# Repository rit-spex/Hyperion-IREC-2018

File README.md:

# IREC-Hyperion

###### Overview
Every year Spaceport America host the Intercollegiate Rocket and Engineering Competition or IREC. Teams for colleges from across the country meet to compete in these events. The 2018 SA Cup will be held June 19-23, 2018, with events held in Las Cruces, NM. RIT SPEX will be partnering with RIT Launch Initiative to deliver our first entry into the competition. Launch Initiative will build the rocket, SPEX will provide the payload. Our goal is to design and build a scientific payload to compete in the intercollegiate rocket engineering competition.

###### Repository Contents

* ***/hardware*** - Hardware design documents
* ***/IREC-Hyperion Documentation*** - Documentation files regarding the Hyperion project
* ***/IREC-Hyperion Drop Test*** - Files regarding drop tests
* ***/IREC-Hyperion HABnet Data Feeder*** - Ground station software which collects data transmitted from payload
* ***/IREC-Hyperion Protocol*** - The Hyperion protocol software library
* ***/IREC-Hyperion System*** - System source files and libraries for the Hyperion payload
* ***/IREC-Hyperion Tests*** - Hyperion test resources 

###### Mission Patch

###### Hardware Modules
- Teensy 3.6
- Sparkfun LIS331
- Sparkfun LSM9DS1
- Adafruit BME280
- Sparkfun CCS811
- RFM_9X LoRa
- PerfectFlite StratoLogger CF

###### Contributors

Daniel Mitchell

Alec Herbert

Thomas James Hall

Dylan R. Wagner

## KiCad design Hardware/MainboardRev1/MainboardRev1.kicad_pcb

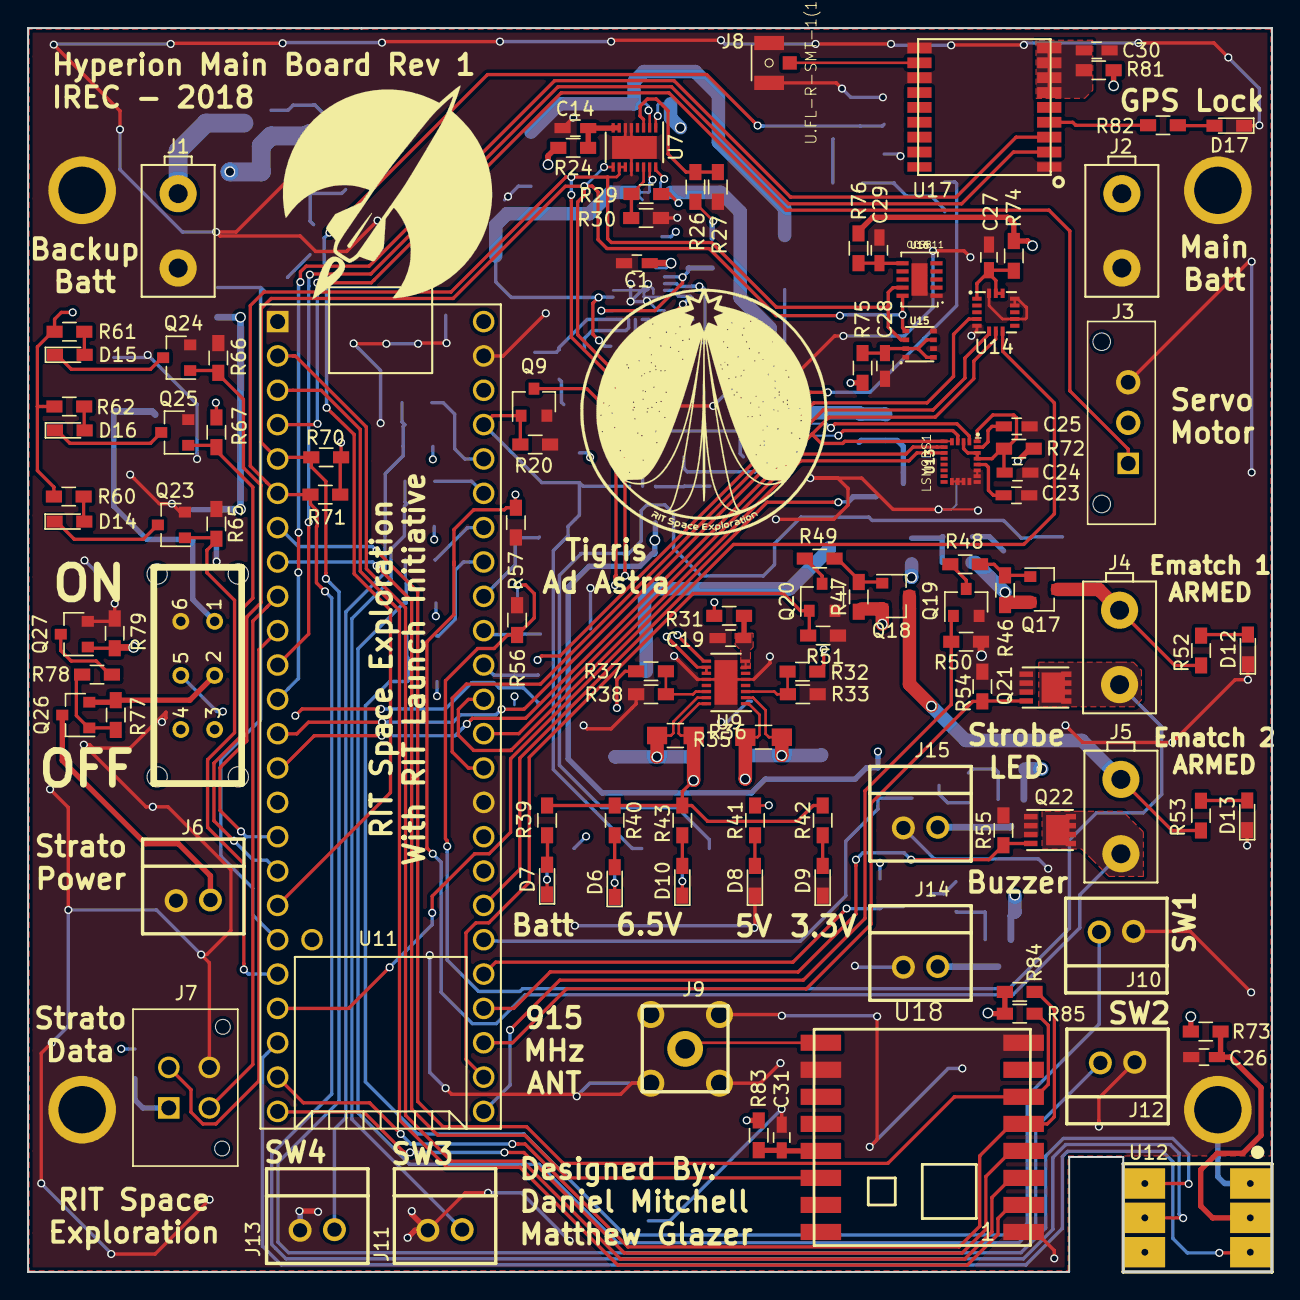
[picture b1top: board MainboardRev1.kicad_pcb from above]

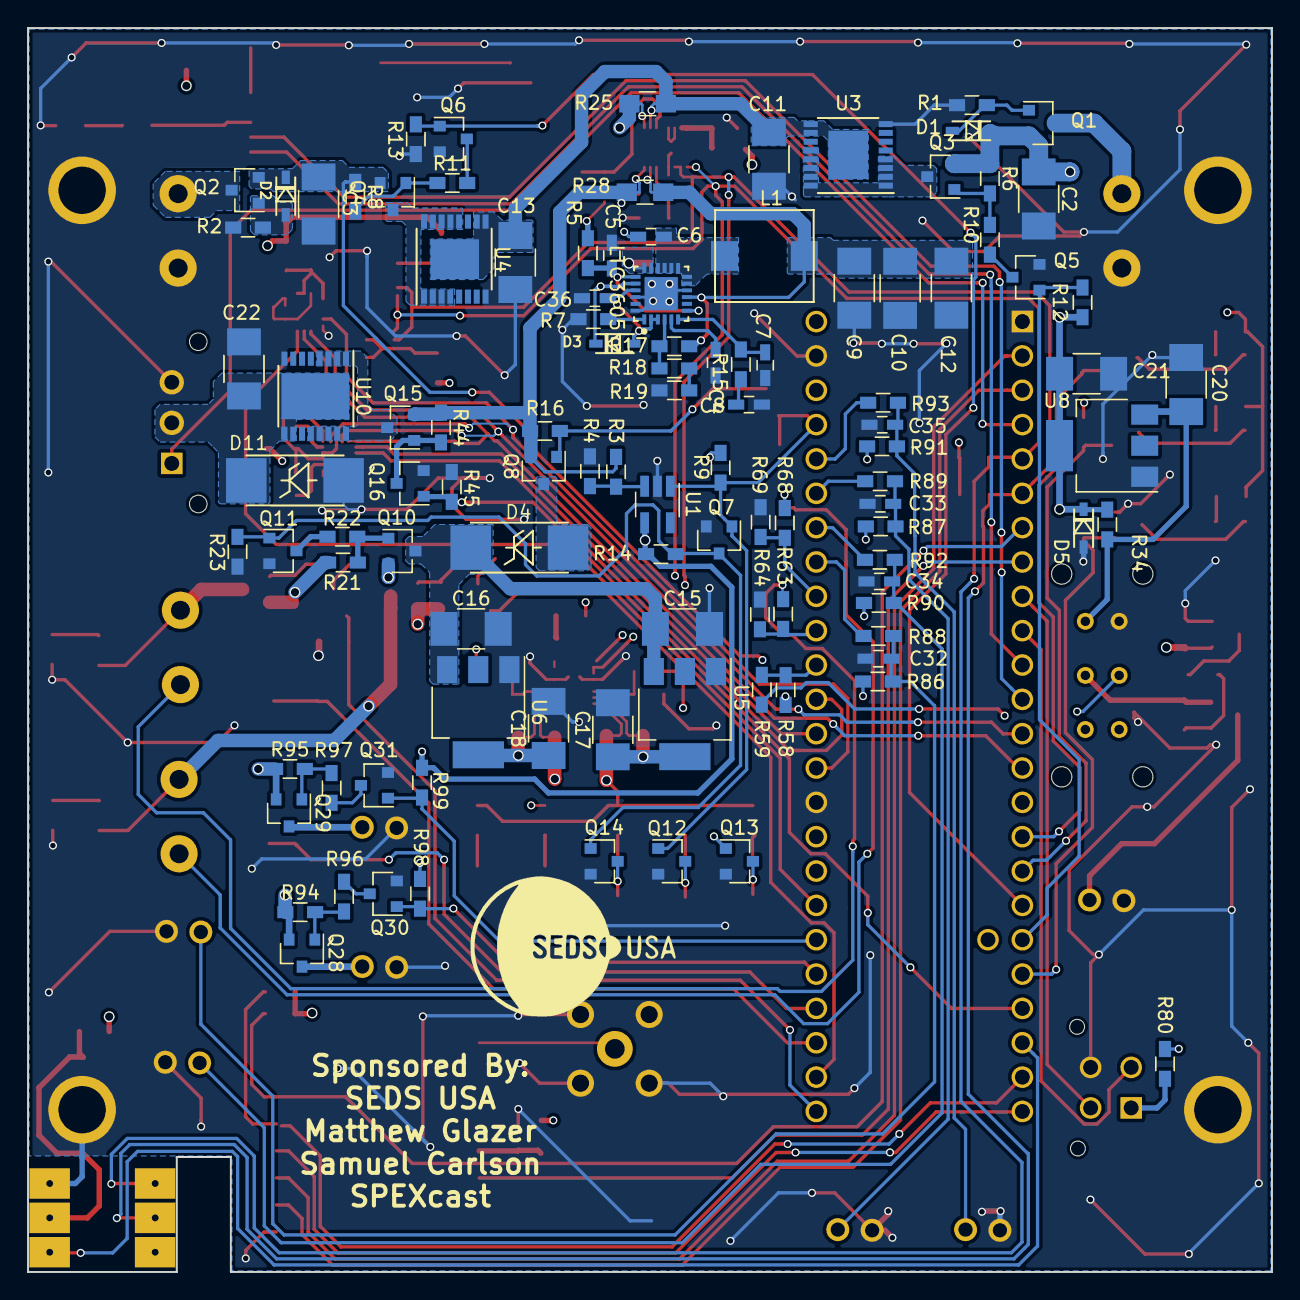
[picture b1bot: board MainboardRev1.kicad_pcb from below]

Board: 4 copper layers, 92.0 x 92.0 mm, 222 parts (106 on the bottom side), 141 nets.

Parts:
C1, C5, C6, C14, C19, C24, C26, C27, C28, C29, C30, C31: 0.1uF; C_0603_HandSoldering
C2, C3, C9, C10, C11, C12, C13, C15, C16, C17, C18, C20, C21, C22: 47uF; C_1210_HandSoldering
C4: .01uF; C_0603_HandSoldering
C7: 10pF; C_0603_HandSoldering
C8: 220pF; C_0603_HandSoldering
C23: 10000pF; C_0603_HandSoldering
C25: 100nF; C_0603_HandSoldering
C32, C33, C34, C35: 10nF; C_0603_HandSoldering
C36: C_0603_HandSoldering
D1, D2: 5.6V; SOD-323_Diode
D3: CMDSH2-3; SOD-323_Diode
D4, D11: SL42-E3/57T; DO-214AB_Zener
D5: +3.3V_Zener; SOD-323_Diode
D6, D7, D8, D9, D14: Green; LED_0603_HandSoldering
D10, D16: Red; LED_0603_HandSoldering
D12, D13: RED; LED_0603_HandSoldering
D15: Blue; LED_0603_HandSoldering
D17: BLUE; LED_0603_HandSoldering
J1: BACKUP_BATT: 1586038-2; CONN_2POS_VERT_TE_CONN
J2: MAIN_BATT: 1586038-2; CONN_2POS_VERT_TE_CONN
J3: Servo_Control; Molex_Microfit3_Header_01x03_Straight
J4: EMATCH_1: 1586038-2; CONN_2POS_VERT_TE_CONN
J5: EMATCH_2: 1586038-2; CONN_2POS_VERT_TE_CONN
J6: Stratologger_PWR: 1586038-2; CONN_2POS_VERT_TE_CONN_LOCK_5-103669-1
J7: Stratologger_DATA; 4-Pin_Molex_Vertical
J8: U.FL-R-SMT-1(10); HRS_U.FL-R-SMT-1(10)
J9: 0733910320 [915MHz SMA]; CONN_RP-SMA_Right_Angle_0733910320
J10: Switch_1; CONN_2POS_VERT_TE_CONN_LOCK_5-103669-1
J11: Switch_3; CONN_2POS_VERT_TE_CONN_LOCK_5-103669-1
J12: Switch_2; CONN_2POS_VERT_TE_CONN_LOCK_5-103669-1
J13: Switch_4; CONN_2POS_VERT_TE_CONN_LOCK_5-103669-1
J14: Buzzer; CONN_2POS_VERT_TE_CONN_LOCK_5-103669-1
J15: Strobe; CONN_2POS_VERT_TE_CONN_LOCK_5-103669-1
L1: RLF7030T-2R2M5R4 [2.2uH]; IND_RLF7030
MH1, MH2, MH3, MH4: Mounting Hole; Mounting_Hole_3.50mm
Q1, Q2, Q3, Q4, Q8, Q10, Q15, Q17, Q18, Q26, Q28, Q29: SSM3J328R; SOT-23
Q5, Q6, Q7, Q9, Q11, Q12, Q13, Q14, Q16, Q19, Q20, Q23, Q24, Q25, Q27, Q30, Q31: NTR4003; SOT-23
Q21, Q22: SIS612EDNT-T1-GE3; PowerPAK_1212-8S
R1, R2, R34: 100k; R_0603_HandSoldering
R3: 140k; R_0603_HandSoldering
R4, R12, R13, R18, R20, R23, R45, R50, R51, R54, R55, R65, R66, R67, R70, R71, R77, R79, R84, R85, R86, R87, R90, R91, R98, R99: 10k; R_0603_HandSoldering
R5, R24, R31, R72, R73, R74, R75, R76, R81, R83: 10; R_0603_HandSoldering
R6, R8, R16, R21, R44, R46, R47, R94, R95: 10K; R_0603_HandSoldering
R7: 200k; R_0603_HandSoldering
R9, R14, R52, R53: 510; R_0603_HandSoldering
R10, R11, R22, R48, R49, R78, R96, R97: 12k; R_0603_HandSoldering
R15: 16k; R_0603_HandSoldering
R17: 118k; R_0603_HandSoldering
R19: 2k; R_0603_HandSoldering
R25, R28: 10m; R_0805_HandSoldering
R26, R29, R32, R37, R56, R57: 1M; R_0603_HandSoldering
R27, R30, R33, R38: 11.5k; R_0603_HandSoldering
R35, R36: 25m; R_0805_HandSoldering
R39, R40, R42, R60, R61, R82: 80; R_0603_HandSoldering
R41: 470; R_0603_HandSoldering
R43, R62: 150; R_0603_HandSoldering
R58, R63, R68: 45.3k; R_0603_HandSoldering
R59, R64, R69: 11.3k; R_0603_HandSoldering
R80: 0; R_0603_HandSoldering
R88, R89, R92, R93: 1k; R_0603_HandSoldering
SW1: EG2201A [DPDT]; SW_DPDT_30V_200mA_EG2201A
U1: LT6703-3; SOT-23-5_HandSoldering
U2: LTC3605; QFN25_4x4mm_0.5mm_pitch
U3, U4: LTC4358; TSSOP-16-1EP_4.4x5mm_Pitch0.65mm
U5: LDL1117S50R; SOT-223_Tab_Pin_2
U6, U8: LDL1117S33R; SOT-223_Tab_Pin_2
U7, U9: LTC2992; DFN-16-1EP_3x4mm_Pitch0.45mm
U10: LTC4358; HTSSOP-16-1EP_4.4x5mm_Pitch0.65mm
U11: Teensy3.6; Teensy33_SidePinsAndVBatt
U12: ABPMANN030PG2A3; PRESSURE_TRANSDUCER_ABPMANN030PG2A3
U13: LSM9DS1; PQFN24P43_350X300X102L35X23N
U14: LIS331HH; LGA16_3x3mm_0.5mm_pitch
U15: BME280
U16: CCS811; SON60P270X400X110-11N
U17: ublox_max-m8q; MAX-M8
U18: RFM69HCW; RFM69HCW-XXXS2

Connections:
+3.3V: Q13.1, R24.2, R31.2, R35.1, R37.1, R67.1, R70.1, R71.1, R72.2, R73.2, R74.2, R75.2, R76.2, R80.2, R81.2, R83.2, R84.1, R85.1, R86.1, R87.1, R90.1, R91.1, U9.1
+3.3V_DIVIDER: R37.2, R38.1, U9.14
+3.3V_MSMT: C18.1, R35.2, U6.2, U9.2
+3.3V_STARTUP: C21.1, D5.1, Q27.1, R9.1, R12.1, R14.1, R34.1, R79.1, R98.1, R99.1, U1.4, U8.2
+5V: R32.1, R36.1, R39.2, R40.1, R42.2, R43.1, R60.2, R61.2, R62.2, U9.16, U11.53
+5V_DIVIDER: R32.2, R33.1, U9.3
+5V_MSMT: C17.1, R36.2, U5.2, U9.15
+6.5V: Q8.2, Q15.2, R3.1, R16.1, R28.1, R29.1, R44.1, U7.16
+6.5V_DIVIDER: R29.2, R30.1, U7.14
+6.5V_MSMT: C9.1, C10.1, C12.1, L1.2, R17.1, R28.2, U2.9, U7.15
BACKUP_BATT: C2.1, D1.1, Q1.2, Q3.2, Q26.2, R6.1, R77.1, SW1.2
BACKUP_BATT_EN: Q5.1, R12.2, U11.19
BATTERY_DIVIDER: R26.2, R27.1, U7.3
BATTERY_PWR: C1.1, Q10.2, Q17.2, Q18.2, Q28.2, Q29.2, R5.2, R21.1, R25.1, R26.1, R41.2, R46.1, R47.1, R94.1, R95.1, U2.17, U2.18, U7.1
BATTERY_PWR_MSMT: C11.1, C13.1, R25.2, U3.9, U3.10, U3.17, U4.9, U4.10, U4.17, U7.2
Buzzer_Disable: Q30.1, R98.2, U11.34
COMMS_CS_LORA: R84.2, U11.23, U18.5
COMMS_MISO: U11.3, U18.2
COMMS_MOSI: U11.2, U18.3
COMMS_RX: U11.11, U17.2
COMMS_SCLK: U11.24, U18.4
COMMS_TX: U11.12, U17.3
CONTROL_1: Q7.1, Q9.1, Q12.1, R9.2, R20.1, U1.1, U11.50
CONTROL_2: Q7.3, Q11.1, Q14.1, R14.2, R23.1
EMATCH_1_ANLG: R63.2, R64.1, U11.44
EMATCH_1_ARM: Q19.1, R50.1, U11.30
EMATCH_1_CHECK: J4.2, Q21.3, R56.1, R63.1
EMATCH_1_FIRE: Q21.1, R54.1, U11.32
EMATCH_2_ANLG: R68.2, R69.1, U11.45
EMATCH_2_ARM: Q20.1, R51.1, U11.31
EMATCH_2_CHECK: J5.2, Q22.3, R57.1, R68.1
EMATCH_2_FIRE: Q22.1, R55.1, U11.33
GND: C1.2, C2.2, C3.2, C4.2, C5.1, C7.2, C8.2, C9.2, C10.2, C11.2, C12.2, C13.2, C14.2, C15.2, C16.2, C17.2, C18.2, C19.2, C20.2, C21.2, C22.2, C23.2, C24.2, C25.2, C26.2, C27.2, C28.2, C29.2, C30.2, C31.2, C32.2, C33.2, C34.2, C35.2, C36.1, D5.2, D8.1, D9.1, D11.2, D12.1, D13.1, D17.1, J1.2, J2.2, J3.3, J6.2, J7.4, J8.2, J9.2, J10.2, J11.2, J12.2, J13.2, J14.2, J15.2, MH1.1, MH2.1, MH3.1, MH4.1, Q5.2, Q6.2, Q7.2, Q9.2, Q11.2, Q12.2, Q13.2, Q14.2, Q16.2, Q19.2, Q20.2, Q21.2, Q22.2, Q23.2, Q24.2, Q25.2, Q27.2, Q30.2, Q31.2, R1.2, R2.2, R4.2, R7.2, R13.2, R19.2, R20.2, R23.2, R27.2, R30.2, R33.2, R38.2, R45.2, R50.2, R51.2, R54.2, R55.2, R56.2, R57.2, R64.2, R65.1, R66.1, R69.2, R79.2, SW1.6, U1.2, U2.10, U2.22, U2.24, U2.25, U3.8, U4.8, U5.1, U6.1, U7.5, U7.6, U7.12, U7.17, U8.1, U9.5, U9.12, U9.17, U10.8, U11.1, U11.39, U11.52, U12.1, U13.14, U13.15, U13.16, U13.17, U13.18, U13.19, U13.20, U14.5, U14.10, U14.12, U14.13, U14.16, U15.1, U15.5, U15.7, U16.1, U16.11, U17.1, U17.10, U17.12, U18.1, U18.8, U18.10
INT_PRESSURE: U11.22, U12.3
LDO_FEED: C15.1, C16.1, D4.1, Q10.3, U5.3, U6.3
LED_BLUE: Q24.1, R66.2, U11.16
LED_GREEN: Q23.1, R65.2, U11.20
LED_RED: Q25.1, R67.2, U11.17
LORA_INT: U11.8, U18.14
LORA_RESET: R85.2, U11.7, U18.6
LSM_C1: C25.1, U13.24
LSM_CAP: C23.1, U13.21
MAIN_BATT: C3.1, D2.1, Q2.2, Q4.2, R8.1, R58.1
MAIN_BATT_ANLG: R58.2, R59.1, U11.43
MAIN_BATT_EN: Q6.1, R13.1, U11.18
MAIN_BATT_READ_EN: R59.2, SW1.5
unnamed: C4.1, U2.5
unnamed: C6.1, D3.1, U2.20
unnamed: C6.2, L1.1, U2.11, U2.12, U2.13, U2.14, U2.15, U2.16
unnamed: C7.1, R15.2, U2.6
unnamed: C8.1, R15.1
unnamed: C14.1, R24.1, U7.7, U7.8
unnamed: C19.1, R31.1, U9.7, U9.8
unnamed: C22.1, D11.1, J3.2, U10.9, U10.10, U10.17
unnamed: C24.1, R72.1, U13.1, U13.3, U13.22, U13.23
unnamed: C26.1, R73.1, U12.2
unnamed: C27.1, R74.1, U14.1, U14.14, U14.15
unnamed: C28.1, R75.1, U15.2, U15.6, U15.8
unnamed: C29.1, R76.1, U16.6
unnamed: C30.1, R81.1, U17.6, U17.7, U17.8, U17.9
unnamed: C31.1, R83.1, U18.13
unnamed: C32.1, J10.1, R86.2, R88.2
unnamed: C33.1, J11.1, R87.2, R89.2
unnamed: C34.1, J12.1, R90.2, R92.2
unnamed: C35.1, J13.1, R91.2, R93.2
unnamed: D1.2, Q1.1, R1.1
unnamed: D2.2, Q2.1, R2.1
unnamed: C36.2, D3.2, U2.2, U2.3, U2.21
unnamed: D4.2, Q8.3
unnamed: D6.1, Q12.3
unnamed: D6.2, R40.2
unnamed: D7.1, Q13.3
unnamed: D7.2, R39.1
unnamed: D8.2, R41.1
unnamed: D9.2, R42.1
unnamed: D10.1, Q14.3
unnamed: D10.2, R43.2
unnamed: D12.2, R52.1
unnamed: D13.2, R53.1
unnamed: D14.1, Q23.3
unnamed: D14.2, R60.1
unnamed: D15.1, Q24.3
unnamed: D15.2, R61.1
unnamed: D16.1, Q25.3
unnamed: D16.2, R62.1
unnamed: D17.2, R82.1
unnamed: J1.1, Q1.3
unnamed: J2.1, Q2.3
unnamed: J4.1, Q17.3, R52.2
unnamed: J5.1, Q18.3, R53.2
unnamed: J6.1, Q26.3
unnamed: J7.1, R80.1
unnamed: J8.1, U17.11
unnamed: J9.1, U18.9
unnamed: J14.1, Q28.3
unnamed: J15.1, Q29.3
unnamed: Q3.1, R6.2, R10.1
unnamed: Q3.3, U3.1, U3.2, U3.3, U3.4, U3.12, U3.13, U3.14, U3.15, U3.16
unnamed: Q4.1, R8.2, R11.1
unnamed: Q4.3, U4.1, U4.2, U4.3, U4.4, U4.12, U4.13, U4.14, U4.15, U4.16
unnamed: Q5.3, R10.2
unnamed: Q6.3, R11.2
unnamed: Q8.1, Q9.3, R16.2
unnamed: Q10.1, R21.2, R22.1
unnamed: Q11.3, R22.2
unnamed: Q15.1, Q16.3, R44.2
unnamed: Q15.3, U10.1, U10.2, U10.3, U10.4, U10.12, U10.13, U10.14, U10.15, U10.16
unnamed: Q17.1, R46.2, R48.1
unnamed: Q18.1, R47.2, R49.1
unnamed: Q19.3, R48.2
unnamed: Q20.3, R49.2
unnamed: Q26.1, R77.2, R78.1
unnamed: Q27.3, R78.2
unnamed: Q28.1, R94.2, R96.1
unnamed: Q29.1, R95.2, R97.1
unnamed: Q30.3, R96.2
unnamed: Q31.3, R97.2
unnamed: R3.2, R4.1, U1.3
unnamed: R7.1, U2.1
unnamed: R17.2, R18.1, U2.4
unnamed: R18.2, R19.1
unnamed: R82.2, U17.4
SENSORS_CS_AG: U11.41, U13.7
SENSORS_CS_LIS: U11.36, U14.8
SENSORS_CS_M: U11.42, U13.8
SENSORS_MISO: U11.14, U13.5, U13.6, U14.7
SENSORS_MOSI: U11.13, U13.4, U14.6
SENSORS_RX: J7.3, U11.9
SENSORS_SCL: R70.2, U7.9, U9.9, U11.5, U12.6, U15.4, U16.10
SENSORS_SCLK: U11.40, U13.2, U14.4
SENSORS_SDA: R71.2, U7.10, U7.11, U9.10, U9.11, U11.6, U12.5, U15.3, U16.9
SENSORS_TX: J7.2, U11.10
SERVO_PWM: J3.1, U11.4
SERVO_PWR_EN: Q16.1, R45.1, U11.21
STARTUP_BATT: C20.1, R34.2, SW1.1, U8.3
SVIN: C5.2, R5.1, U2.7, U2.19
SWITCH_1: R88.1, U11.46
SWITCH_2: R92.1, U11.47
SWITCH_3: R89.1, U11.48
SWITCH_4: R93.1, U11.49
Strobe_Disable: Q31.1, R99.2, U11.35

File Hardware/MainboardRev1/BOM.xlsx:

RIT Space Exploration - Hyperion Scientific Payload for the Intercollegiate Roc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
Ref | Description | Manf Part Number | Manf | Footprint | Purchase Link | Quantity | Price | Sub Total
C4 C23 C32 C33 C34 C35 | .01uF, 100V |  |  | 0603 | Digikey
C1 C5 C6 C14 C19 C24 C25 C26 C27 C28 C29 C30 C31 | 0.1uF, 50V |  |  | 0603 | Digikey
C7 | 10pF, 25V |  |  | 0603 | Digikey
C8 | 220pF, 100V |  |  | 0603 | Digikey
C2 C3 C9 C10 C11 C12 C13 C15 C16 C17 C18 C20 C21 C22 | 47uF, 16V |  |  | 1210 | Digikey
D5 | 3.3V Zener |  |  |  | Digikey
D1 D2 | 5.6V Zener |  |  |  | Digikey
D3 | Schottky Diode (Switching Regulator) |  |  |  | Digikey
D15 D17 | Blue LED | 3.3Vf, 20mA, 104mcd |  |  | Digikey
D6 D7 D8 D9 D14 | Green LED | 3.4Vf, 10mA, 98mcd |  |  | Digikey
D10 D12 D13 D16 | Red LED | 2Vf, 20mA, 104mcd |  |  | Digikey
D4 D11 | Schottky Diode 20V 4A |  |  |  | Digikey
J9 |  | CONN_RP-SMA_Right_Angle_0733910320 |  |  | Digikey
J1 J2 J4 J5 |  | CONN_2POS_VERT_TE_CONN |  |  | Digikey
Mates for Above |  |  |  |  | Digikey
J6 J10 J11 J12 J13 J14 J15 |  |  |  |  | Digikey
Mates for Above |  |  |  |  | Digikey
J3 |  | Molex_Microfit3_Header_01x03_Straight |  |  | Digikey
Mates for Above |  |  |  |  | Digikey
J7 |  | 4-Pin_Molex_Vertical |  |  | Digikey
Mates for Above |  |  |  |  | Digikey
J8 |  | HRS_U.FL-R-SMT-1(10) |  |  | Digikey
TE Connectivity AMP Pins |  |  |  |  | Digikey
Other TE Connectivity Pins??? |  |  |  |  | Digikey
Molex Pins |  |  |  |  | Digikey
 |  |  |  |  |  | 0 |  | 0
L1 | 2.2uH | RLF7030T-2R2M5R4 |  |  | Digikey
 |  |  |  |  |  | 0 |  | 0
Q5 Q6 Q7 Q9 Q11 Q12 Q13 Q14 Q16 Q19 Q20 Q23 Q24 Q25 Q27 Q30 Q31 |  | NTR4003 |  |  | Digikey
Q21 Q22 |  | SIS612EDNT-T1-GE3 |  |  | Digikey
Q1 Q2 Q3 Q4 Q8 Q10 Q15 Q17 Q18 Q26 Q28 Q29 |  | SSM3J328R |  |  | Digikey
 |  |  |  |  |  | 0 |  | 0
R80 | 0 | 0 |  |  | Digikey
R5 R24 R31 R72 R73 R74 R75 R76 R81 R83 | 10 | 10 |  |  | Digikey
R1 R2 R34 | 100k | 100k |  |  | Digikey
R4 R6 R8 R12 R13 R16 R18 R20 R21 R23 R44 R45 R46 R47 R50 R51 R54 R55 R65 R66 R6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 | 10k | 10k |  |  | Digikey
R25 R28 | 10m | 10m |  |  | Digikey
R59 R64 R69 | 11.3k | 11.3k |  |  | Digikey
R27 R30 R33 R38 | 11.5k | 11.5k |  |  | Digikey
R17 | 118k | 118k |  |  | Digikey
R10 R11 R22 R48 R49 R78 R96 R97 | 12k | 12k |  |  | Digikey
R3 | 140k | 140k |  |  | Digikey
R43 R62 | 150 | 150 |  |  | Digikey
R15 | 16k | 16k |  |  | Digikey
R26 R29 R32 R37 R56 R57 | 1M | 1M |  |  | Digikey
R88 R89 R92 R93 | 1k | 1k |  |  | Digikey
R7 | 200k | 200k |  |  | Digikey
R35 R36 | 25m | 25m |  |  | Digikey
R19 | 2k | 2k |  |  | Digikey
R58 R63 R68 | 45.2k | 45.3k |  |  | Digikey
R41 | 470 | 470 |  |  | Digikey
R9 R14 R52 R53 | 510 | 510 |  |  | Digikey
R39 R40 R42 R60 R61 R82 | 80 | 80 |  |  | Digikey
 |  |  |  |  |  | 0 |  | 0
SW1 |  |  |  |  | Digikey
 |  |  |  |  |  | 0 |  | 0
U12 |  |  | ABPMANN030PG2A3 |  | Digikey
U15 |  |  | BME280 |  | Digikey
U16 |  |  | CCS811
U6 U8 |  |  | LDL1117S33R |  | Digikey
U5 |  |  | LDL1117S50R |  | Digikey
U14 |  |  | LIS331HH |  | Digikey
U13 |  |  | LSM9DS1 |  | Digikey
U1 |  |  | LT6703-3 |  | Digikey
U7 U9 |  |  | LTC2992 |  | Digikey
U2 |  |  | LTC3605 |  | Digikey
U3 U4 U10 |  |  | LTC4358 |  | Digikey
U18 |  |  | RFM69HCW |  | Digikey
U11 |  |  | Teensy3.6 |  | N/A
U17 |  |  | ublox_max-m8q |  | Digikey
 |  |  |  |  |  | 0 |  | 0
ANTENNA |  |  |  |  | Digikey
 |  |  |  |  |  | 0 |  | 0
 |  |  |  |  |  | Total Cost |  | 0

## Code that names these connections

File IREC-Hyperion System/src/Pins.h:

/*
 * Hyperion - IREC
 * File: Pins.h
 * Organization: RIT Space Exploration
 * Description
 *    Header file used to define pins with corresponding macros.
 */

#ifndef PINS_H
#define PINS_H

// PCB Pins

#define COMMS_MOSI      0
#define COMMS_MISO      1
#define SERVO_PWM       2
#define SENSORS_SCL     3
#define SENSORS_SDA     4
#define LORA_RST        5
#define LORA_INT        6
#define SENSORS_RX      7
#define SENSORS_TX      8
#define COMMS_RX        9
#define COMMS_TX        10
#define SENSORS_MOSI    11
#define SESNORS_MISO    12
#define SENSORS_SCLK    13
#define SENSORS_CS_AG   14
#define SENSORS_CS_M    15
#define MAIN_BATT_ANLG  16
#define EMATCH_1_ANLG   17
#define EMATCH_2_ANLG   18
#define SWITCH_01       19
#define SWITCH_02       20
#define SWITCH_03       21
#define SWITCH_04       22
#define CONTROL_1       23
#define LED_BLUE        24
#define LED_RED         25
#define MAIN_BATT_EN    26
#define BACKUP_BATT_EN  27
#define LED_GREEN       28
#define SERVO_PWR_EN    29
#define INT_PRESSURE    30
#define COMMS_CS_LORA   31
#define COMMS_SCLK      32
#define EMATCH_1_ARM    33
#define EMATCH_2_ARM    34
#define EMATCH_1_FIRE   35
#define EMATCH_2_FIRE   36
#define BUZZER_DISABLE  37
#define STROBE_DISABLE  38
#define SENSOR_CS_LIS   39

// PROTO_PINS
/**
#define RFM95_INT       4  
#define RFM95_CS        5 
#define RFM95_RST       6
#define LSM9DS1_M_CS    10 
#define LIS3DH_MOSI     11
#define LIS3DH_MISO     12
#define LIS3DH_CLK      13
#define HEARTBEAT_LED   22
#define LSM9DS1_AG_CS   24
#define DEPLOY_SWITCH_01 25 
#define DEPLOY_SWITCH_02 26 
#define DEPLOY_SWITCH_03 27 
#define DEPLOY_SWITCH_04 28 
#define EMATCH_1_ARM_P    23
#define EMATCH_1_FIRE_P   21
#define LIS3DH_CS        35
*/

#endif
 

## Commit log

2018-01-28 added list331 project folder
2018-01-28 BME280
2018-01-28 Added LSM9DS1 read code
2018-01-29 Project init
2018-01-29 .DS_Store PURGED FOR GOOD!
2018-01-29 PURGED old dirs
2018-01-29 Renamed
2018-01-29 Flushed out some sensor functions
2018-01-29 Finshed IRECHYPERION_LSM9DS1.ino
2018-01-29 Added support for BME280
2018-01-29 Updated Readme with sensor info
2018-01-30 Updated documentation
2018-01-31 Moved Test file
2018-01-31 Created dirs + Updated README.md
2018-01-31 Reworked getter functions in LSM9DS1
2018-02-01 Obligatory Update Readme.md
2018-02-04 added file for reading from the CCS811 gas sensor (assisted by BME280)
2018-02-04 made lis331 work
2018-02-11 Achieved LORA communication
2018-02-11 Updataed README.md
2018-02-12 Changed file names
2018-02-12 Added TX code
2018-02-18 Created new DIR
2018-02-18 Added readme
2018-02-25 Updated Hyperion Protocol
2018-02-25 Added Hardware Folder and Initialized Mainboard Project
2018-03-11 Updated functions in LSM file and refactored CCS811 file. Added a routine .ino file
2018-03-11 Created header and corres cpp file
2018-03-12 Updated Hyperion Functions, Completed packing functions for the LSM9DS1, BME280 and CCS811 data groups.
2018-03-12 Added function prototypes and files to the Hyperion System
2018-03-13 Worked on unpacking function for the header and LSM9DS1
2018-03-14 Added system functionality, Flushed out more unpacking functions within the Hyperion Protocol
2018-03-15 Woring on communication
2018-03-16 Updated trasnmit routine for the BME280 and flushed out some Buffer functions
2018-03-16 Updated system
2018-03-16 Updated protocol code
2018-03-16 Fixed data conversions
2018-03-18 Worked on buffer utils
2018-03-18 Added transmit code
2018-03-18 Updated test code
2018-03-18 Finished R_seq_LSM9DS1_data routine and it's helper function
2018-03-20 Converted source files to work with platformIO
2018-03-20 Cleaning dirs
2018-03-20 Added RadioHead
2018-03-21 Updated readme.txt
2018-03-22 Added Software Status report 01 - 03/22/2018
2018-03-22 Added some more circuitry to power schematic
2018-03-23 Updated CCS811 file with utility functions. Added a utility function file for the LIS331 Sensor.
2018-03-23 Updated function prototypes
2018-03-23 Worked on seq routines for the LSM9DS1 and the BME280
2018-03-23 Added the bme seq to the startup
2018-03-27 Renamed test
2018-03-27 removed test
2018-03-27 Added string bulider test file
2018-03-27 Cleaned up code
2018-03-29 Added deployment routines
2018-03-31 Updated read triggers on the deployment switches from LOW to HIGH. Added thoughts on R_mission_constraints routine
2018-03-31 Changed depoyment error case
2018-03-31 Added utils prototypes for the LIS331
2018-04-02 Added utility function to find the rate of climb and finished the deployment routine.
2018-04-03 Fixed init prints
2018-04-03 Removed some print statements
2018-04-03 Added timing to logged data
2018-04-03 Added SD card support
2018-04-03 Added FILE_NAME define
2018-04-03 Increased preformance of SD I/O
2018-04-04 Cleaned up test dir
2018-04-04 added some (untested) code for measuring accelerometer data during a drop test
2018-04-04 added matlab script for reading and displaying drop test CSV data
2018-04-05 Updated program to use two DSQs one for a suspened state and one for armed state
2018-04-05 Added execution ref
2018-04-06 Added seq and trans routines for the CCS811 sensor. Updated main code to work with phase swaping.
2018-04-07 Updated documentation, Added utils functions for LIS331
2018-04-07 Updated README.md and re arranged dirs
2018-04-07 Added R_seq_LIS331_data()
2018-04-07 Working on strato logger code
2018-04-08 Updated LIS331 code
2018-04-08 Completed Stratologger code
2018-04-08 Finshed StratoLogger Routine
2018-04-08 Added init code for Stratologger
2018-04-09 R_check_deployment is more readable now
2018-04-09 Tested Stratologger code
2018-04-09 Worked on Auto Arm code
2018-04-09 Changed max priotity for StratoLogger Routine
2018-04-09 Added a Readme.md file to system dir
2018-04-09 Updated .gitignore
2018-04-10 Updated execution ref
2018-04-11 Fixed SPI buss hoging issue and added a better Radio-Head Libary
2018-04-11 added unpack code for CCS811
2018-04-13 Updated deployment configuration
2018-04-13 Updated lib readme
2018-04-13 Removed print
2018-04-15 Parachute test
2018-04-16 Worked on deployment code
2018-04-16 Worked on altitude routines
2018-04-17 Worked on writing to file
2018-04-17 Working on mission events
2018-04-18 Worked on mission events routine
2018-04-18 Fixded spelling and documentation
2018-04-18 Worked on Hyperion protocol
2018-04-19 Added transmit code for LIS331 and Altitude data
2018-04-19 Updated documentation on routine function
2018-04-19 Test rx code now accepts more data frames
2018-04-19 Updated transmit code with "fix"
2018-04-20 Removed Serial prints
2018-04-21 Updated priority mult
2018-04-22 Updated serial
2018-04-24 Upped write speed
2018-04-24 Tested SD card write speeds
2018-04-24 Added transmit scaler
2018-04-24 Commented out trans code
2018-04-24 Added seperate header files
2018-04-24 Moved routine defines
2018-04-25 Added Heartbeat routine
2018-04-25 Updated macros for buffer
2018-04-25 Inital commit
2018-04-25 Added paul's radiohead lib
2018-04-26 Tested deployment code and adjusted deployment macros.
2018-04-26 Adjusted macros
2018-05-05 Added string buliding code for the LSM9DS1 and BME280
2018-05-05 Finshed handle messages function.
2018-05-14 Schematic Finished. Needs Review & Final Touches. Beginning Footprints...:
2018-05-16 Added a pin header file
2018-05-16 Small changes to schematic: Added voltage dividers for analog inputs, small net changes. Added footprints for each part
2018-05-16 PCB outline
2018-05-17 Completed parachute deployment routine.
2018-05-17 Enabled some routines
2018-05-17 added script for sending data from a ground station to a HABnet instance
2018-05-17 Added more packing and unpacking functions to the Hyperion Protocol
2018-05-17 Added arm and disarm routines.
2018-05-17 Added orentation transmit routine.
2018-05-17 Updated notes
2018-05-17 Components placed. Needs to be routed.
2018-05-17 Modified SPI busses, added more error checking to launch detect function.
2018-05-17 Added proto-ground station
2018-05-18 Added to silkscreen. Updated schematic pdf
2018-05-18 Created deployment test
2018-05-18 Added heartBeat to test
2018-05-18 Added yaw to system and oren routines
2018-05-18 Updated test with Dan's changes.
2018-05-18 Added LoRa init test
2018-05-19 Fixed init test
2018-05-19 Updated HeartBeat Pins
2018-05-19 More silk screen updates
2018-05-19 Disabled some sensor routines temp
2018-05-19 Altered para pins
2018-05-19 Rearanged command seq
2018-05-19 Reduced HeartBeat mult value
2018-05-19 Added init call for parapins
2018-05-19 Added armed conf
2018-05-19 Updated protocol
2018-05-20 Added health utils
2018-05-20 Completed work on deployment check
2018-05-20 Enabled disabled routines
2018-05-20 Added pin blocking to arm routine
2018-05-20 Added documentation
2018-05-20 Moved LSM9DS1 and LIS331 back to SPI1
2018-05-20 Enabled CCS811 init
2018-05-20 Updated proto-ground station to accept info messages
2018-05-20 Updated protoground station
2018-05-20 Removed a hiden folder
2018-05-20 Updated arm routine with changes from proto-payload
2018-05-20 GS now only sends one command per input
2018-05-20 GS now only sends one update per command
2018-05-20 Added software debuff on arm sequence and updated pins to match PCB
2018-05-20 Updated RadioHead Lib to drop packets if busy.
2018-05-20 Reintroduced bandwidth sliding
2018-05-20 Added led pin logic
2018-05-20 Added notes
2018-05-21 Renamed DEBUFF to DEBOUNCE
2018-05-22 Updated switch debouncing to include precentage thresholds.
2018-05-22 Recreated R_check_deployment routine.
2018-05-23 Added buzzer and strobe LED. Created BOM. Reannotated. Added sponsors to silkscreen. Needs to be routed and sent out. Good luck Matt!
2018-05-23 started routing PCB
2018-05-23 Added a bunch of random libraries and footprints. What you need should be in there somewhere
2018-05-24 continued work on routing, plenty of work still to be done
    commiting my work for the night
2018-05-24 Modified Heatbeat routine to maintain set interval.
2018-05-24 Added cast to threshold calculation
2018-05-24 Updated launch detect function to work using only alititude, Stratolo
2018-05-24 morning work, continued routing
    shifted some components slightly for better trace routing, so far so good
2018-05-24 committing progress, estimating the board is approx 1/3 routed
2018-05-25 All routing except for the antenna connections is finished
2018-05-25 Updated pins
2018-05-25 Added some more routines
2018-05-25 Added strobe and delay routines + buzzer enables and disables
2018-05-25 Added TinyGPS lib for ublox max-m8q
2018-05-25 Added R_trans_GPS to routines .h file
2018-05-25 Added GPS files
2018-05-25 Removed .vscode folder
2018-05-26 Added some ground station code for arming/disarming
2018-05-27 System Forwarder is now complete.
2018-05-27 Added simulation function for oren
2018-05-28 added gerbers and an image of the board
2018-05-28 fixed trace width issues relating to the IMU, routed the antenna traces
2018-05-29 changed to work with a teensy 3.6
2018-05-29 fixed bugs with sending orientation data
2018-05-29 reworked and split into separate files
2018-05-29 added another (shorter) flag for each argument
2018-05-29 fixed copy/paste error in requirements
2018-05-29 updated and added better details for arguments
2018-05-29 added link to System Forwarder and fixed typos
2018-05-29 PCB updated per the DFM checks
    via and trace width changes, changed to meet the requirments per the manufacturer's abilities
2018-05-29 updated gerbers based on PCB changes
2018-06-01 added dict to be used for file names
2018-06-01 now a subclass of Thread, added functions so it can recieve data
2018-06-01 split functionality into separate threads, added file writting & input command reading
2018-06-01 added details arg to readme
2018-06-07 Added alt sim
2018-06-07 FIxed for Alec
2018-06-07 Sorry alec fixed now
2018-06-07 Fixed conversion to string issue
2018-06-07 ignore bad data
2018-06-07 fix some incorrect data keys & convert to values to integers
2018-06-08 Added some sim funcs for Alec
2018-06-08 fixed typo in simulation code
2018-06-08 can now ignore some repeated parts of recieved data (only when sending to habnet)
2018-06-08 important file io changes. makes sure dar directory exists & buffers are flushed
2018-06-13 removed sim
2018-06-13 Fixed
2018-06-14 Blocked lora bug
2018-06-14 Lora test
2018-06-14 lora init fail msg
2018-06-15 Changed BME280 buss
2018-06-15 Fixed some addresses
2018-06-16 Added check to prevent certain packets of data to get sent to habnet
2018-06-16 Added Batt/Ematch Checking
2018-06-17 Fixed power routine
2018-06-17 Fixed CC811 init
2018-06-17 Updated routines
2018-06-17 Added TX RX5 fix
2018-06-17 Fixed syn
2018-06-17 Fixed messages
2018-06-17 Beep
2018-06-17 Added more logic to arm
2018-06-17 Fixed import
2018-06-17 Removed timeout
2018-06-17 Set idle block
2018-06-17 Made Dan changes
2018-06-17 Added more delays to para
2018-06-17 Removed Test Code
2018-06-17 Added Gps test
2018-06-17 Added new GPS lib
2018-06-18 Added print for info
2018-06-19 Print all
2018-06-19 Added health reporting
2018-06-19 Added print
2018-06-19 Changed BME280 alt update threshold
2018-06-19 Added init checks
2018-06-19 Fixed converion issure
2018-06-19 Fixed conversion alt error
2018-06-19 Updated sea level pressure for NEW MEXICO
2018-06-20 Addded GPS transmission
2018-06-20 Added gps time
2018-06-20 Added gps fix
2018-06-20 added gps code to done phase
2018-06-22 Disabled launch detect and orentation transmission.
2018-06-22 Adjusted deployment macros
2018-06-27 Anaysis
2018-07-23 Fixed data
2018-07-25 Added time series plots
2018-07-27 Fixed naming issue
